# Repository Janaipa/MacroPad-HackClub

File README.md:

# MacroPad-HackClub

## Overview
This project is a custom macropad featuring a 3x4 keyboard, 1 rotary encoder and a 0.91 inch OLED display.

## 📂 Repository Structure
```
3D Model/          # 3D models (Fusion 360)
Electrical Design/ # KiCad PCB anb schematic files
Firmware/          # file .ino
```
## PCB

## 3D Preview

## BOM
- 11x Cherry MX Switches
- 11x Blank DSA Keycaps (White)
- 1x EC-11 Rotary Encoder
- 1x 0.91 inch OLED display
- 12x 1N4148 Diodes
- 2x 10kOhm Resistor
- 2x 1kOhm Resistor
- 2x 0.1uF Capacitor
- 1x XIAO RP2040
- 1x Case (2 printed parts)

## 📝License
This project is licensed under the **GNU General Public License v2.0**.  
You can read the full text in the [`LICENSE`](LICENSE) file or at [gnu.org](https://www.gnu.org/licenses/gpl-2.0.html).

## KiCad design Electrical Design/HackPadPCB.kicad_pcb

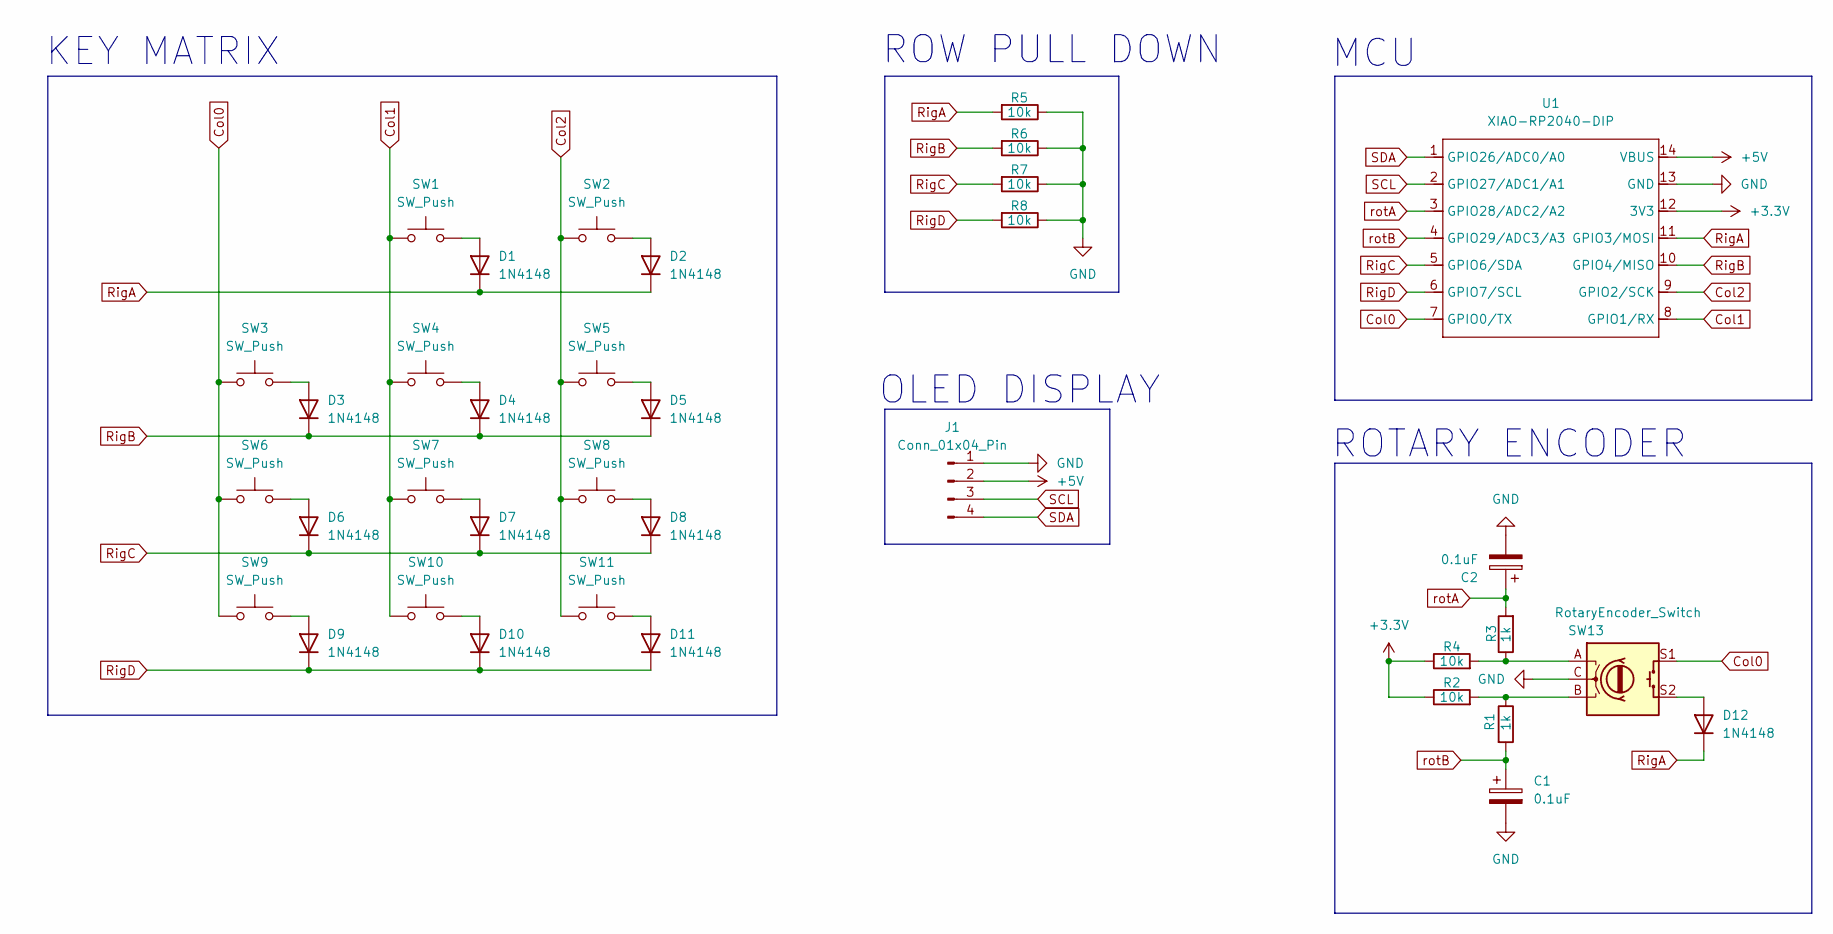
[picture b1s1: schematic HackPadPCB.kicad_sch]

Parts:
C1, C2: 0.1uF; CP_Radial_D4.0mm_P2.00mm
D1, D2, D3, D4, D5, D6, D7, D8, D9, D10, D11, D12: 1N4148; D_DO-35_SOD27_P7.62mm_Horizontal
J1: Conn_01x04_Pin; SSD1306-0.91-OLED-4pin-128x32
R1, R3: 1k; R_Axial_DIN0207_L6.3mm_D2.5mm_P7.62mm_Horizontal
R2, R4, R5, R6, R7, R8: 10k; R_Axial_DIN0207_L6.3mm_D2.5mm_P7.62mm_Horizontal
SW1, SW2, SW3, SW4, SW5, SW6, SW7, SW8, SW9, SW10, SW11: SW_Push; SW_Cherry_MX_1.00u_PCB
SW13: RotaryEncoder_Switch; RotaryEncoder_Alps_EC11E-Switch_Vertical_H20mm
U1: XIAO-RP2040-DIP

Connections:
+3.3V: R2.1, R4.1, U1.12 (3V3)
+5V: J1.2, U1.14 (VBUS)
Col0: SW3.1, SW6.1, SW9.1, SW13.S1, U1.7 (GPIO0/TX)
Col1: SW1.1, SW4.1, SW7.1, SW10.1, U1.8 (GPIO1/RX)
Col2: SW2.1, SW5.1, SW8.1, SW11.1, U1.9 (GPIO2/SCK)
GND: C1.2, C2.2, J1.1, R5.1, R6.1, R7.1, R8.1, SW13.C, U1.13 (GND)
unnamed: D1.2 (A), SW1.2
unnamed: D2.2 (A), SW2.2
unnamed: D3.2 (A), SW3.2
unnamed: D4.2 (A), SW4.2
unnamed: D5.2 (A), SW5.2
unnamed: D6.2 (A), SW6.2
unnamed: D7.2 (A), SW7.2
unnamed: D8.2 (A), SW8.2
unnamed: D9.2 (A), SW9.2
unnamed: D10.2 (A), SW10.2
unnamed: D11.2 (A), SW11.2
unnamed: D12.2 (A), SW13.S2
unnamed: R1.1, R2.2, SW13.B
unnamed: R3.1, R4.2, SW13.A
RigA: D1.1 (K), D2.1 (K), D12.1 (K), R5.2, U1.11 (GPIO3/MOSI)
RigB: D3.1 (K), D4.1 (K), D5.1 (K), R6.2, U1.10 (GPIO4/MISO)
RigC: D6.1 (K), D7.1 (K), D8.1 (K), R7.2, U1.5 (GPIO6/SDA)
RigD: D9.1 (K), D10.1 (K), D11.1 (K), R8.2, U1.6 (GPIO7/SCL)
SCL: J1.3, U1.2 (GPIO27/ADC1/A1)
SDA: J1.4, U1.1 (GPIO26/ADC0/A0)
rotA: C2.1, R3.2, U1.3 (GPIO28/ADC2/A2)
rotB: C1.1, R1.2, U1.4 (GPIO29/ADC3/A3)

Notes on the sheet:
ROW PULL DOWN
KEY MATRIX
OLED DISPLAY
ROTARY ENCODER
MCU

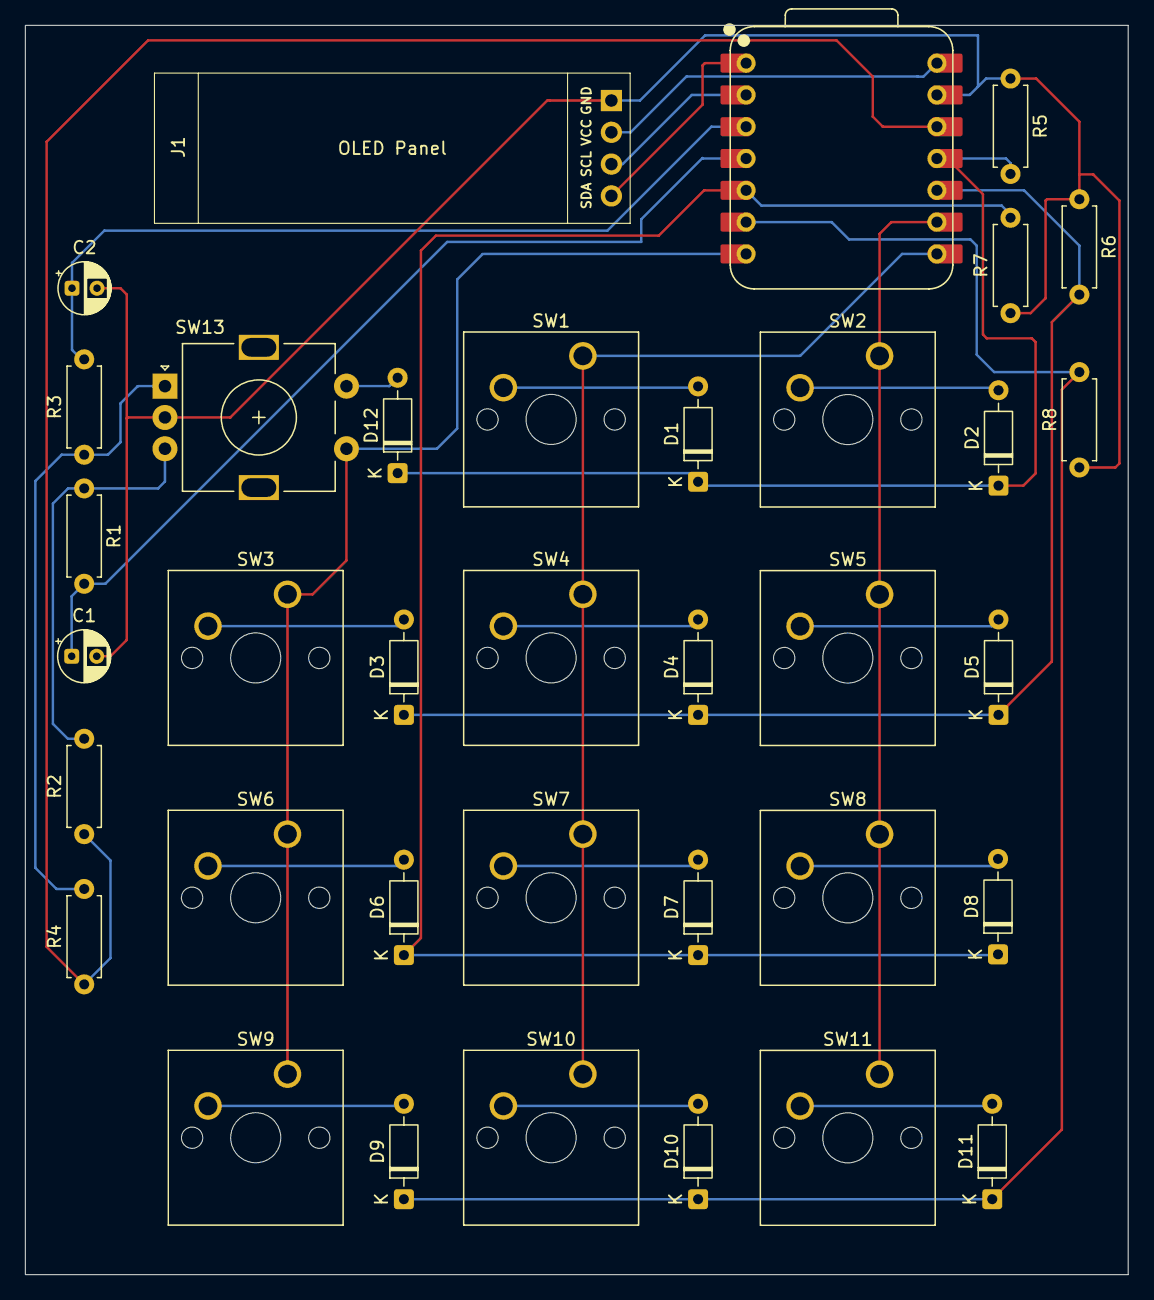
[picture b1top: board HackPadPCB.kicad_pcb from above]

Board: 2 copper layers, 88.1 x 99.8 mm, 36 parts (0 on the bottom side), 28 nets.

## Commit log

2025-12-15 Create folder eletrical design
2025-12-15 upload of kicad file
2025-12-15 Create folder 3D Model
2025-12-15 Update README.md
    overview
    repository structure (3d model, electrical design)
    license
2025-12-15 Update README.md
    / after electrical design
2025-12-22 upload of 3d model file (.step & .f3d)
2025-12-24 Create test
2025-12-24 Added firmware
2025-12-26 Update PCB
2025-12-26 Update README.md
    3d preview
2025-12-26 Update Top Case
